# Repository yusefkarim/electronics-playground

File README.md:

# Electronics Playground

## Projects

### [ESP32-C3 Peter Board](./esp32c3-peter-board)

* Purpose: for me to get familiar with KiCad and PCB design
* Component overview:
   - ESP32-C3 (ESP32-C3-WROOM-02-H4)
   - Microphone (CMC-5042PF-AC) and amplifier (MAX4466EXK)
   - Photo diode (TEMT6000X01)
   - Humidity and pressure sensor (BME280)
   - SD card (GSD090012SEU)
   - Additional on-board flash memory (W25Q32JVSSIQ)
   - USB (Type-C) connector (only for power delivery)
   - Battery Charge Management Controller (MCP73871)
   - Proper 3.3V voltage regulation (LM1117MPX-3.3)
* Designed following Peter Dalmaris' tutorial: [KiCad 9: Design & assemble an ESP32 IoT 4-layer PCB](https://www.youtube.com/watch?v=LO9AO0XTX3M)
* Also incorporated knowledge from Peter's online course and book: [KiCad Like a Pro 3rd edition](https://techexplorations.com/so/kicad-like-a-pro-3rd-edition/)

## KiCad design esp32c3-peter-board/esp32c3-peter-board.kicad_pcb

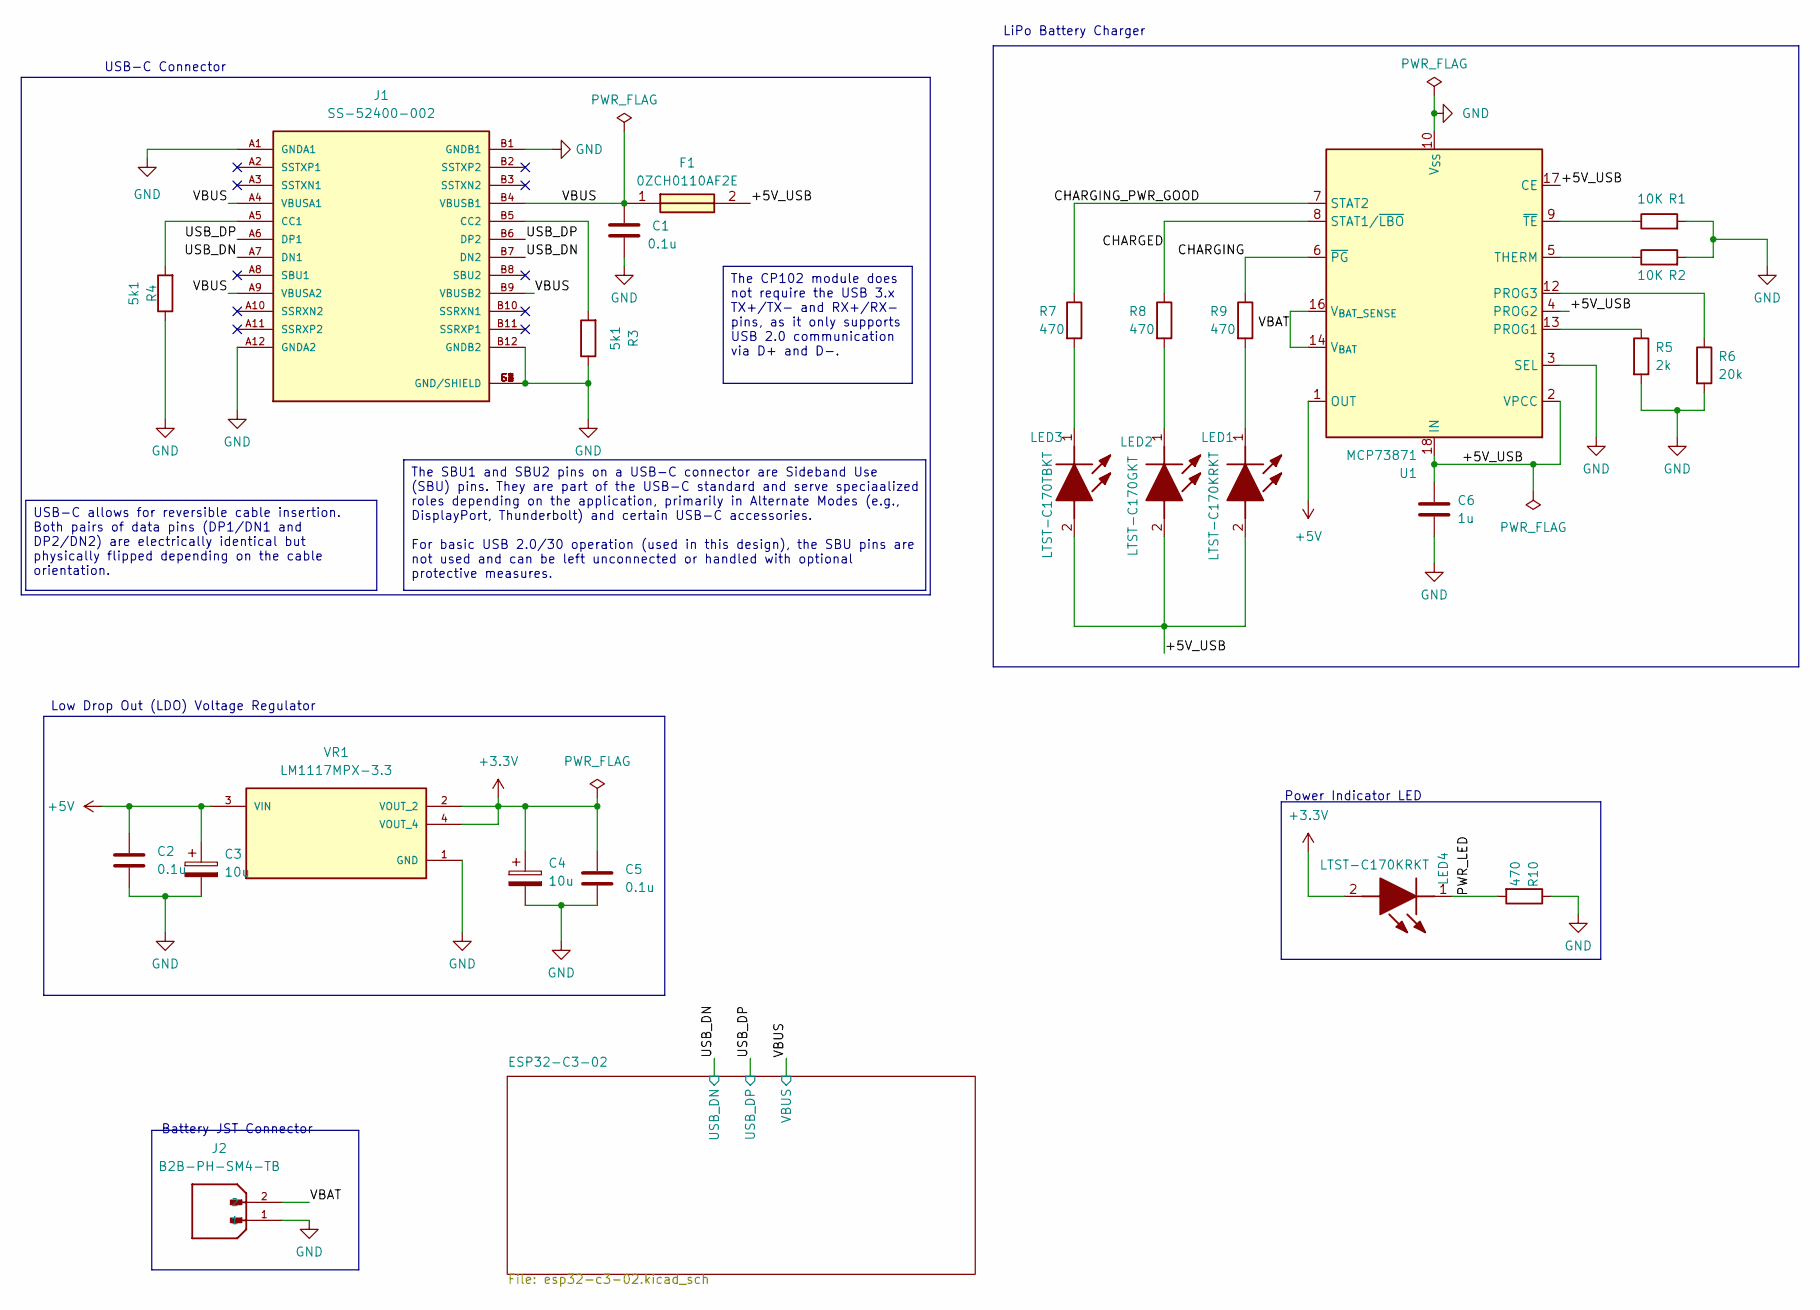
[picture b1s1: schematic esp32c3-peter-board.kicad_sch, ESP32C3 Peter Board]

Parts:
C1, C2, C5: 0.1u; C_0805_2012Metric
C3, C4: 10u; T491A
C6: 1u; C_0805_2012Metric
F1: 0ZCH0110AF2E; FUSC3226X100N; Manufacturer_Part_Number 0ZCH0110AF2E
J1: SS-52400-002; BELFUSE_SS-52400-002; PARTREV A0
J2: B2B-PH-SM4-TB; JST_B2B-PH-SM4-TB; PARTREV N/A
LED1, LED4: LTST-C170KRKT; LEDC2012X120N; Manufacturer_Part_Number LTST-C170KRKT; Mouser Part Number 859-LTST-C170KRKT
LED2: LTST-C170GKT; LEDC2012X120N; Manufacturer_Part_Number LTST-C170GKT; Mouser Part Number 859-LTST-C170GKT
LED3: LTST-C170TBKT; LEDC2012X120N; Manufacturer_Part_Number LTST-C170TBKT; Mouser Part Number 859-LTST-C170TBKT
R1, R2: 10K; R_0805_2012Metric
R3, R4: 5k1; R_0805_2012Metric
R5: 2k; R_0805_2012Metric
R6: 20k; R_0805_2012Metric
R7, R8, R9, R10: 470; R_0805_2012Metric
U1: MCP73871; QFN-20-1EP_4x4mm_P0.5mm_EP2.5x2.5mm
VR1: LM1117MPX-3.3; VREG_LM1117MPX-3.3

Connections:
+3.3V: C4.1, C5.1, LED4.2 (A), VR1.2 (VOUT_2), VR1.4 (VOUT_4); also elsewhere on the board
+5V: C2.1, C3.1, U1.1 (OUT), U1.20 (OUT), VR1.3 (VIN)
/+5V_USB: C6.1, F1.2, LED1.2 (A), LED2.2 (A), LED3.2 (A), U1.2 (VPCC), U1.4 (PROG2), U1.17 (CE), U1.18 (IN), U1.19 (IN)
/CHARGED: R8.1, U1.8 (STAT1/~LBO)
/CHARGING: R9.1, U1.6 (~PG)
/CHARGING_PWR_GOOD: R7.1, U1.7 (STAT2)
/PWR_LED: LED4.1 (K), R10.2
/USB_DN: J1.A7 (DN1), J1.B7 (DN2); also elsewhere on the board
/USB_DP: J1.A6 (DP1), J1.B6 (DP2); also elsewhere on the board
/VBAT: J2.2, U1.14 (V_{BAT}), U1.15 (V_{BAT}), U1.16 (V_{BAT_SENSE})
/VBUS: C1.1, F1.1, J1.A4 (VBUSA1), J1.A9 (VBUSA2), J1.B4 (VBUSB1), J1.B9 (VBUSB2); also elsewhere on the board
GND: C1.2, C2.2, C3.2, C4.2, C5.2, C6.2, J1.A1 (GNDA1), J1.A12 (GNDA2), J1.B1 (GNDB1), J1.B12 (GNDB2), J1.G1 (GND/SHIELD), J1.G2 (GND/SHIELD), J1.G3 (GND/SHIELD), J1.G4 (GND/SHIELD), J1.S1 (GND/SHIELD), J1.S2 (GND/SHIELD), J1.S3 (GND/SHIELD), J1.S4 (GND/SHIELD), J2.1, R1.2, R2.2, R3.1, R4.1, R5.2, R6.2, R10.1, U1.3 (SEL), U1.10 (V_{SS}), U1.11 (V_{SS}), U1.21 (V_{SS}), VR1.1 (GND); also elsewhere on the board
unnamed: J1.A5 (CC1), R4.2
unnamed: J1.B5 (CC2), R3.2
unnamed: LED1.1 (K), R9.2
unnamed: LED2.1 (K), R8.2
unnamed: LED3.1 (K), R7.2
unnamed: R5.1, U1.13 (PROG1)
unnamed: R6.1, U1.12 (PROG3)
unnamed: R2.1, U1.5 (THERM)
unnamed: R1.1, U1.9 (~TE)

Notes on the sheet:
LiPo Battery Charger
Power Indicator LED
USB-C Connector
Low Drop Out (LDO) Voltage Regulator
Battery JST Connector
The SBU1 and SBU2 pins on a USB-C connector are Sideband Use (SBU) pins. They are part of the USB-C standard and serve speciaalized roles depending on the application, primarily in Alternate Modes (e.g., DisplayPort, Thunderbolt) and certain USB-C accessories. For basic USB 2.0/30 operation (used i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
USB-C allows for reversible cable insertion. Both pairs of data pins (DP1/DN1 and DP2/DN2) are electrically identical but physically flipped depending on the cable orientation.
The CP102 module does not require the USB 3.x TX+/TX- and RX+/RX- pins, as it only supports USB 2.0 communication via D+ and D-.

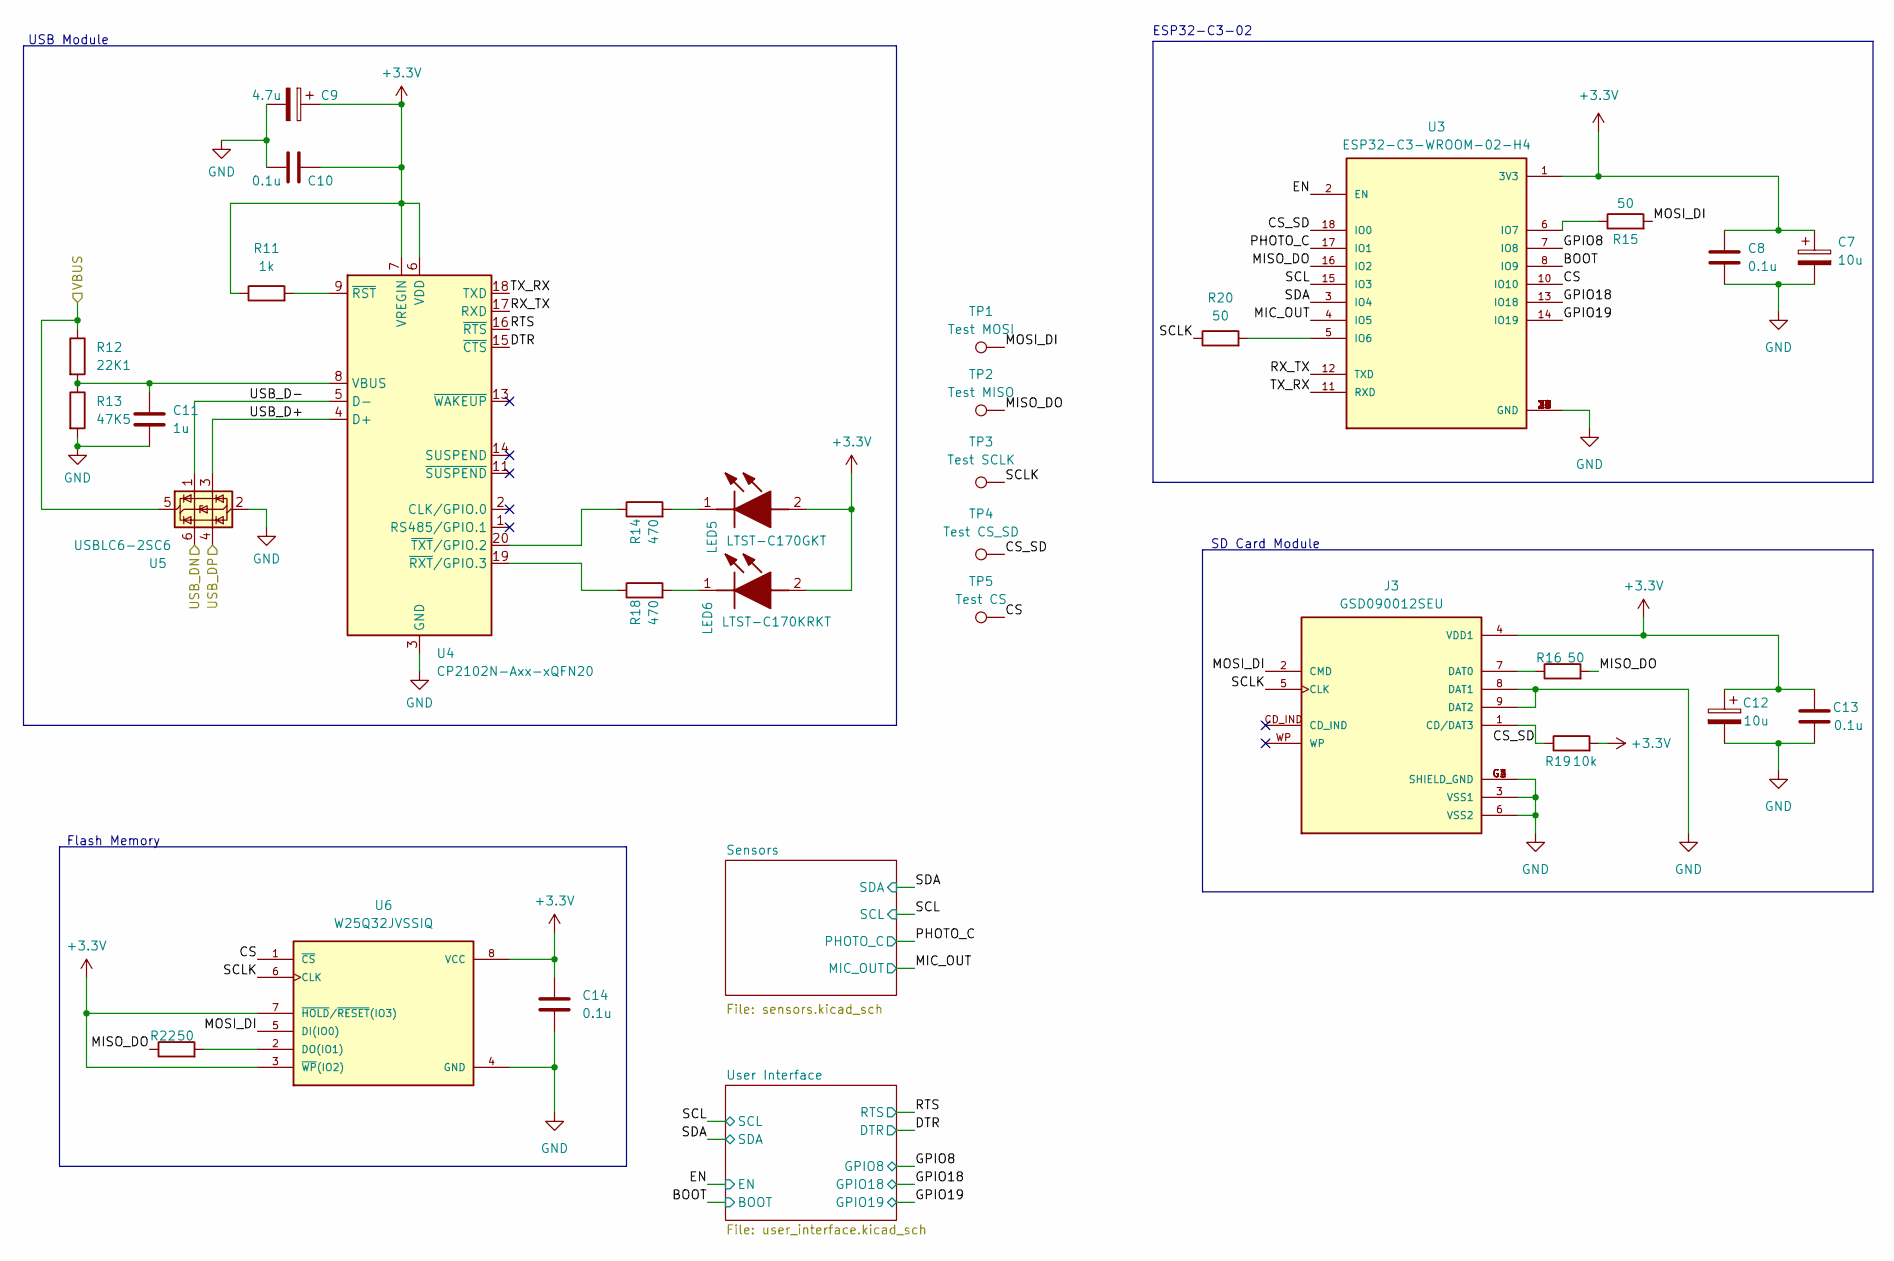
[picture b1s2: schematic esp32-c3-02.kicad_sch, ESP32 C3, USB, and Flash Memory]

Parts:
C7, C12: 10u; T491A
C8, C10, C13, C14: 0.1u; C_0805_2012Metric
C9: 4.7u; T491A
C11: 1u; C_0805_2012Metric
J3: GSD090012SEU; AMPHENOL_GSD090012SEU; PARTREV E
LED5: LTST-C170GKT; LEDC2012X120N; Manufacturer_Part_Number LTST-C170GKT; Mouser Part Number 859-LTST-C170GKT
LED6: LTST-C170KRKT; LEDC2012X120N; Manufacturer_Part_Number LTST-C170KRKT; Mouser Part Number 859-LTST-C170KRKT
R11: 1k; R_0805_2012Metric
R12: 22K1; R_0805_2012Metric
R13: 47K5; R_0805_2012Metric
R14, R18: 470; R_0805_2012Metric
R15, R16, R20, R22: 50; R_0805_2012Metric
R19: 10k; R_0805_2012Metric
TP1: Test MOSI; TestPoint_Pad_D1.0mm
TP2: Test MISO; TestPoint_Pad_D1.0mm
TP3: Test SCLK; TestPoint_Pad_D1.0mm
TP4: Test CS_SD; TestPoint_Pad_D1.0mm
TP5: Test CS; TestPoint_Pad_D1.0mm
U3: ESP32-C3-WROOM-02-H4; MODULE_ESP32-C3-WROOM-02-H4
U4: CP2102N-Axx-xQFN20; SiliconLabs_QFN-20-1EP_3x3mm_P0.5mm_EP1.8x1.8mm
U5: USBLC6-2SC6; SOT-23-6
U6: W25Q32JVSSIQ; SOIC127P790X216-8N; M_PART_NUMBER W25QXX

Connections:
+3.3V: C7.1, C8.1, C9.1, C10.2, C12.1, C13.1, C14.1, J3.4 (VDD1), LED5.2 (A), LED6.2 (A), R11.1, R19.2, U3.1 (3V3), U4.6 (VDD), U4.7 (VREGIN), U6.3 (~WP(IO2)), U6.7 (~HOLD/~RESET(IO3)), U6.8 (VCC); also elsewhere on the board
/ESP32-C3-02/BOOT: U3.8 (IO9); also elsewhere on the board
/ESP32-C3-02/CS: TP5.1, U3.10 (IO10), U6.1 (~CS)
/ESP32-C3-02/CS_SD: J3.1 (CD/DAT3), R19.1, TP4.1, U3.18 (IO0)
/ESP32-C3-02/DTR: U4.15 (~CTS); also elsewhere on the board
/ESP32-C3-02/EN: U3.2 (EN); also elsewhere on the board
/ESP32-C3-02/GPIO8: U3.7 (IO8); also elsewhere on the board
/ESP32-C3-02/GPIO18: U3.13 (IO18); also elsewhere on the board
/ESP32-C3-02/GPIO19: U3.14 (IO19); also elsewhere on the board
/ESP32-C3-02/MIC_OUT: U3.4 (IO5); also elsewhere on the board
/ESP32-C3-02/MISO_DO: R16.2, R22.1, TP2.1, U3.16 (IO2)
/ESP32-C3-02/MOSI_DI: J3.2 (CMD), R15.2, TP1.1, U6.5 (DI(IO0))
/ESP32-C3-02/PHOTO_C: U3.17 (IO1); also elsewhere on the board
/ESP32-C3-02/RTS: U4.16 (~RTS); also elsewhere on the board
/ESP32-C3-02/RX_TX: U3.12 (TXD), U4.17 (RXD)
/ESP32-C3-02/SCL: U3.15 (IO3); also elsewhere on the board
/ESP32-C3-02/SCLK: J3.5 (CLK), R20.1, TP3.1, U6.6 (CLK)
/ESP32-C3-02/SDA: U3.3 (IO4); also elsewhere on the board
/ESP32-C3-02/TX_RX: U3.11 (RXD), U4.18 (TXD)
/ESP32-C3-02/USB_D+: U4.4 (D+), U5.3 (I/O2)
/ESP32-C3-02/USB_D-: U4.5 (D-), U5.1 (I/O1)
/USB_DN: U5.6 (I/O1); also elsewhere on the board
/USB_DP: U5.4 (I/O2); also elsewhere on the board
/VBUS: R12.1, U5.5 (VBUS); also elsewhere on the board
GND: C7.2, C8.2, C9.2, C10.1, C11.2, C12.2, C13.2, C14.2, J3.3 (VSS1), J3.6 (VSS2), J3.8 (DAT1), J3.9 (DAT2), J3.G1 (SHIELD_GND), J3.G2 (SHIELD_GND), J3.G3 (SHIELD_GND), J3.G4 (SHIELD_GND), R13.2, U3.9 (GND), U3.19 (GND), U3.20 (GND), U3.21 (GND), U3.22 (GND), U3.23 (GND), U3.24 (GND), U3.25 (GND), U3.26 (GND), U3.27 (GND), U3.28 (GND), U3.29 (GND), U3.30 (GND), U3.31 (GND), U3.32 (GND), U3.33 (GND), U3.34 (GND), U3.35 (GND), U3.36 (GND), U3.37 (GND), U3.38 (GND), U3.39 (GND), U4.3 (GND), U4.12 (GND), U4.21 (GND), U5.2 (GND), U6.4 (GND); also elsewhere on the board
unnamed: J3.7 (DAT0), R16.1
unnamed: LED5.1 (K), R14.2
unnamed: LED6.1 (K), R18.2
unnamed: R20.2, U3.5 (IO6)
unnamed: R15.1, U3.6 (IO7)
unnamed: C11.1, R12.2, R13.1, U4.8 (VBUS)
unnamed: R11.2, U4.9 (~RST)
unnamed: R18.1, U4.19 (~RXT/GPIO.3)
unnamed: R14.1, U4.20 (~TXT/GPIO.2)
unnamed: R22.2, U6.2 (DO(IO1))

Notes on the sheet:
ESP32-C3-02
Flash Memory
SD Card Module
USB Module

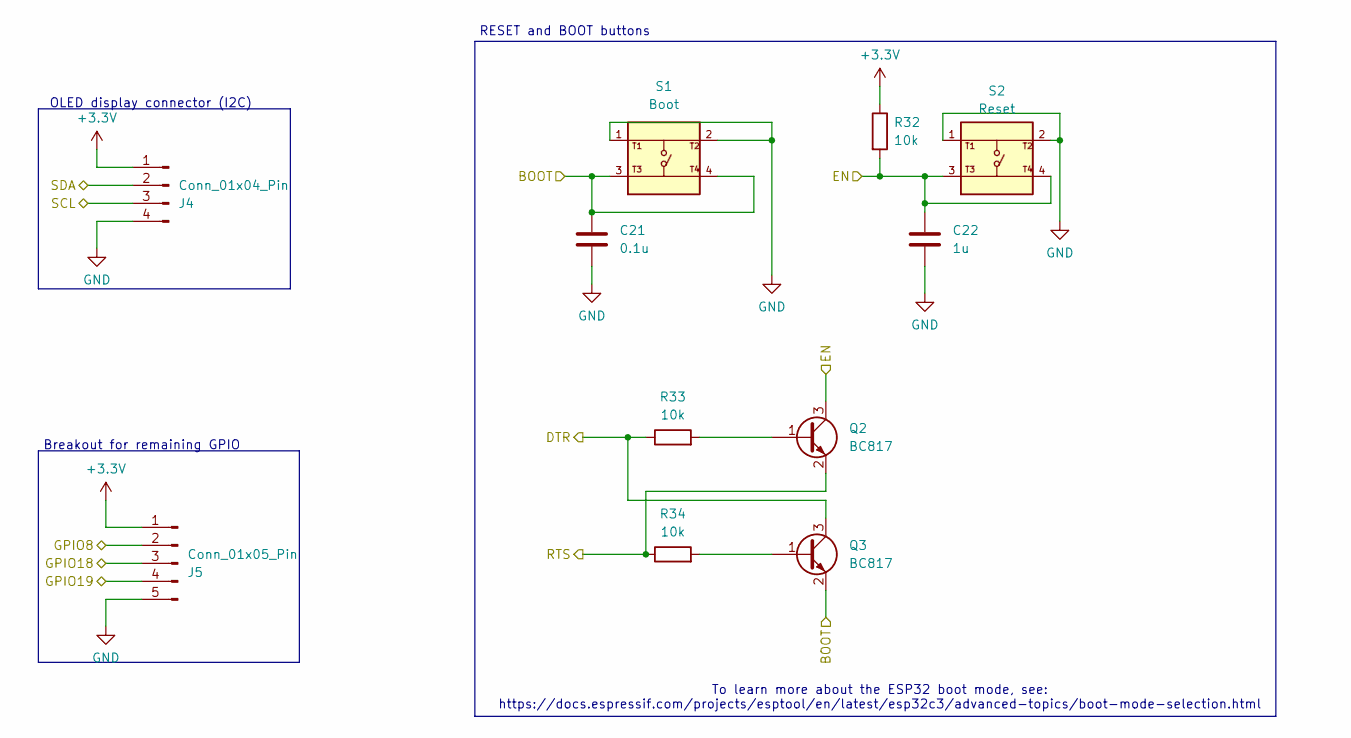
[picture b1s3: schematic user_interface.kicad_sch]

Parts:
C21: 0.1u; C_0805_2012Metric
C22: 1u; C_0805_2012Metric
J4: Conn_01x04_Pin; PinHeader_1x04_P2.54mm_Vertical
J5: Conn_01x05_Pin; PinHeader_1x05_P2.54mm_Vertical
Q2, Q3: BC817; SOT-23
R32, R33, R34: 10k; R_0805_2012Metric
S1: Boot; SW_USLPT2819DT2TR; PARTREV P
S2: Reset; SW_USLPT2819DT2TR; PARTREV P

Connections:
+3.3V: J4.1, J5.1, R32.1; also elsewhere on the board
/ESP32-C3-02/BOOT: C21.1, Q3.2 (E), S1.3, S1.4; also elsewhere on the board
/ESP32-C3-02/DTR: Q3.3 (C), R33.1; also elsewhere on the board
/ESP32-C3-02/EN: C22.1, Q2.3 (C), R32.2, S2.3, S2.4; also elsewhere on the board
/ESP32-C3-02/GPIO8: J5.2; also elsewhere on the board
/ESP32-C3-02/GPIO18: J5.3; also elsewhere on the board
/ESP32-C3-02/GPIO19: J5.4; also elsewhere on the board
/ESP32-C3-02/RTS: Q2.2 (E), R34.1; also elsewhere on the board
/ESP32-C3-02/SCL: J4.3; also elsewhere on the board
/ESP32-C3-02/SDA: J4.2; also elsewhere on the board
GND: C21.2, C22.2, J4.4, J5.5, S1.1, S1.2, S2.1, S2.2; also elsewhere on the board
unnamed: Q2.1 (B), R33.2
unnamed: Q3.1 (B), R34.2

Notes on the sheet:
Breakout for remaining GPIO
OLED display connector (I2C)
To learn more about the ESP32 boot mode, see: https://docs.espressif.com/projects/esptool/en/latest/esp32c3/advanced-topics/boot-mode-selection.html
RESET and BOOT buttons

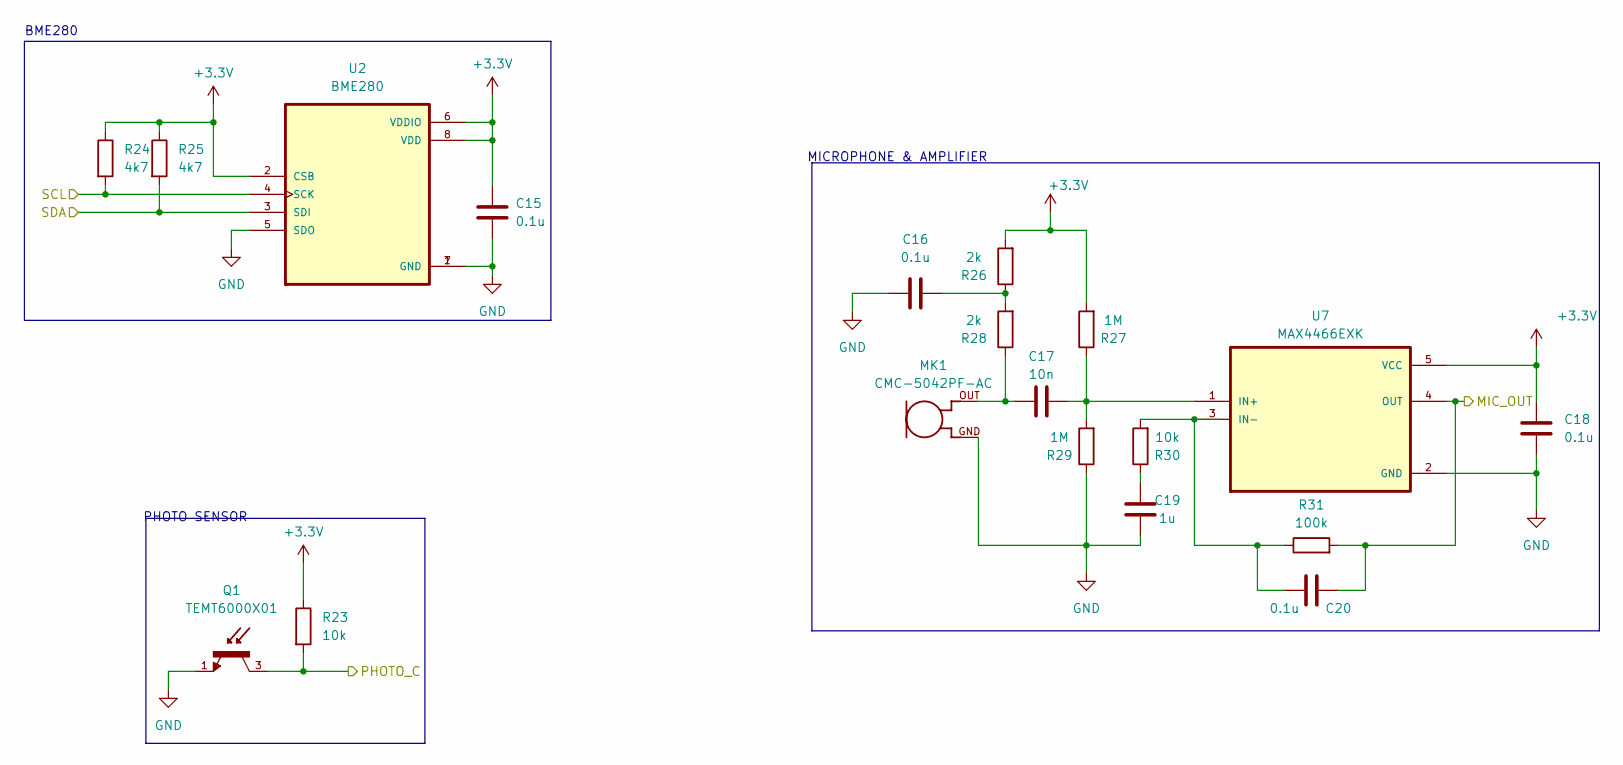
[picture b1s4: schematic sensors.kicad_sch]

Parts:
C15, C16, C18, C20: 0.1u; C_0805_2012Metric
C17: 10n; C_0805_2012Metric
C19: 1u; C_0805_2012Metric
MK1: CMC-5042PF-AC; CUI_CMC-5042PF-AC
Q1: TEMT6000X01; TRANS_TEMT6000X01; PARTREV 1.9
R23, R30: 10k; R_0805_2012Metric
R24, R25: 4k7; R_0805_2012Metric
R26, R28: 2k; R_0805_2012Metric
R27, R29: 1M; R_0805_2012Metric
R31: 100k; R_0805_2012Metric
U2: BME280; PSON65P250X250X100-8N
U7: MAX4466EXK; SOT65P210X110-5N

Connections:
+3.3V: C15.1, C18.1, R23.1, R24.1, R25.1, R26.2, R27.2, U2.2 (CSB), U2.6 (VDDIO), U2.8 (VDD), U7.5 (VCC); also elsewhere on the board
/ESP32-C3-02/MIC_OUT: C20.2, R31.2, U7.4 (OUT); also elsewhere on the board
/ESP32-C3-02/PHOTO_C: Q1.3, R23.2; also elsewhere on the board
/ESP32-C3-02/SCL: R24.2, U2.4 (SCK); also elsewhere on the board
/ESP32-C3-02/SDA: R25.2, U2.3 (SDI); also elsewhere on the board
GND: C15.2, C16.2, C18.2, C19.1, MK1.GND, Q1.1, R29.1, U2.1 (GND), U2.5 (SDO), U2.7 (GND), U7.2 (GND); also elsewhere on the board
unnamed: C16.1, R26.1, R28.2
unnamed: C17.2, MK1.OUT, R28.1
unnamed: C19.2, R30.1
unnamed: C17.1, R27.1, R29.2, U7.1 (IN+)
unnamed: C20.1, R30.2, R31.1, U7.3 (IN-)

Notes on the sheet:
MICROPHONE & AMPLIFIER
BME280
PHOTO SENSOR

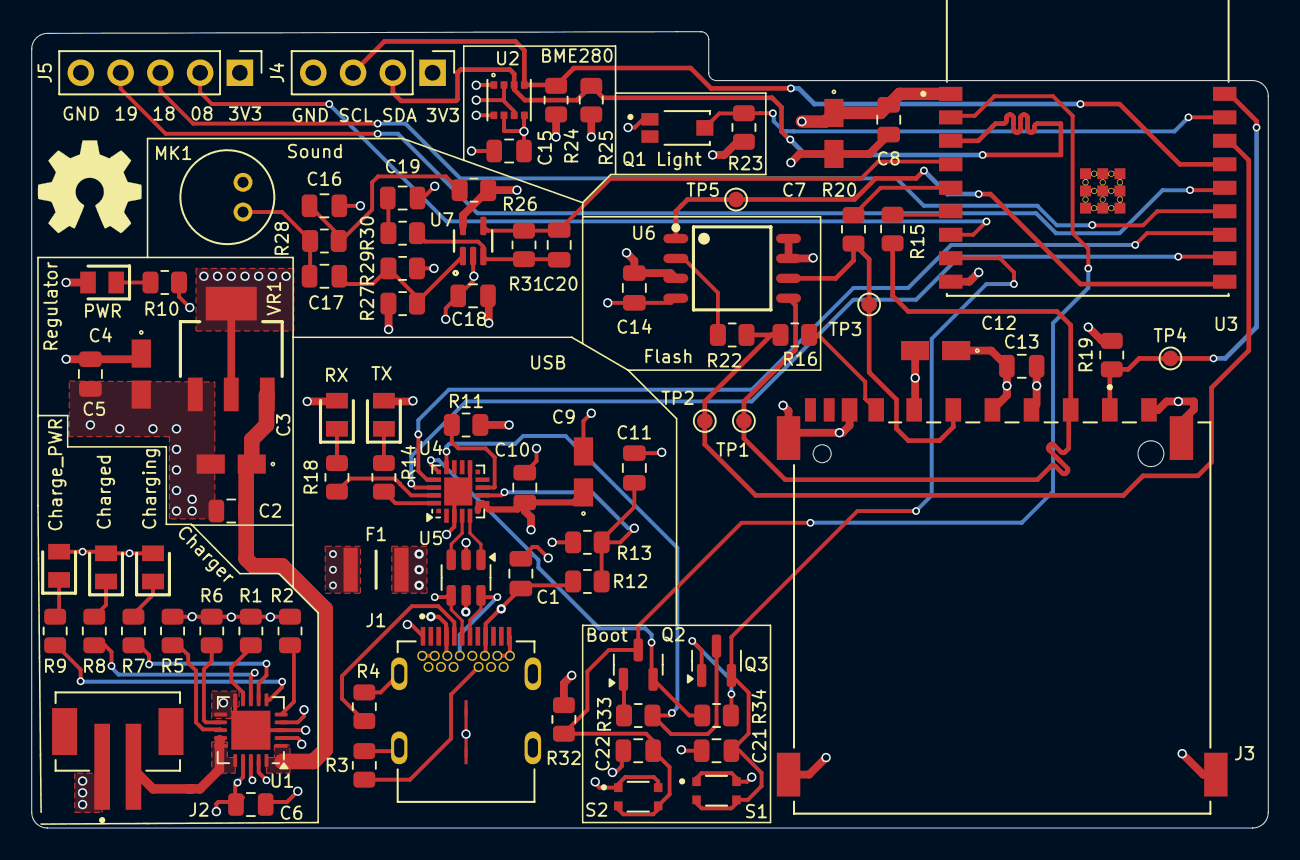
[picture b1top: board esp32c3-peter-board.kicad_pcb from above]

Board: 4 copper layers, 79.0 x 50.9 mm, 85 parts (0 on the bottom side), 58 nets.

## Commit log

2025-06-08 Add docs
2025-06-08 Add esp32c3-peter-board
2025-06-08 Add README.md
2025-06-08 Add esp32c3-peter-board project image
